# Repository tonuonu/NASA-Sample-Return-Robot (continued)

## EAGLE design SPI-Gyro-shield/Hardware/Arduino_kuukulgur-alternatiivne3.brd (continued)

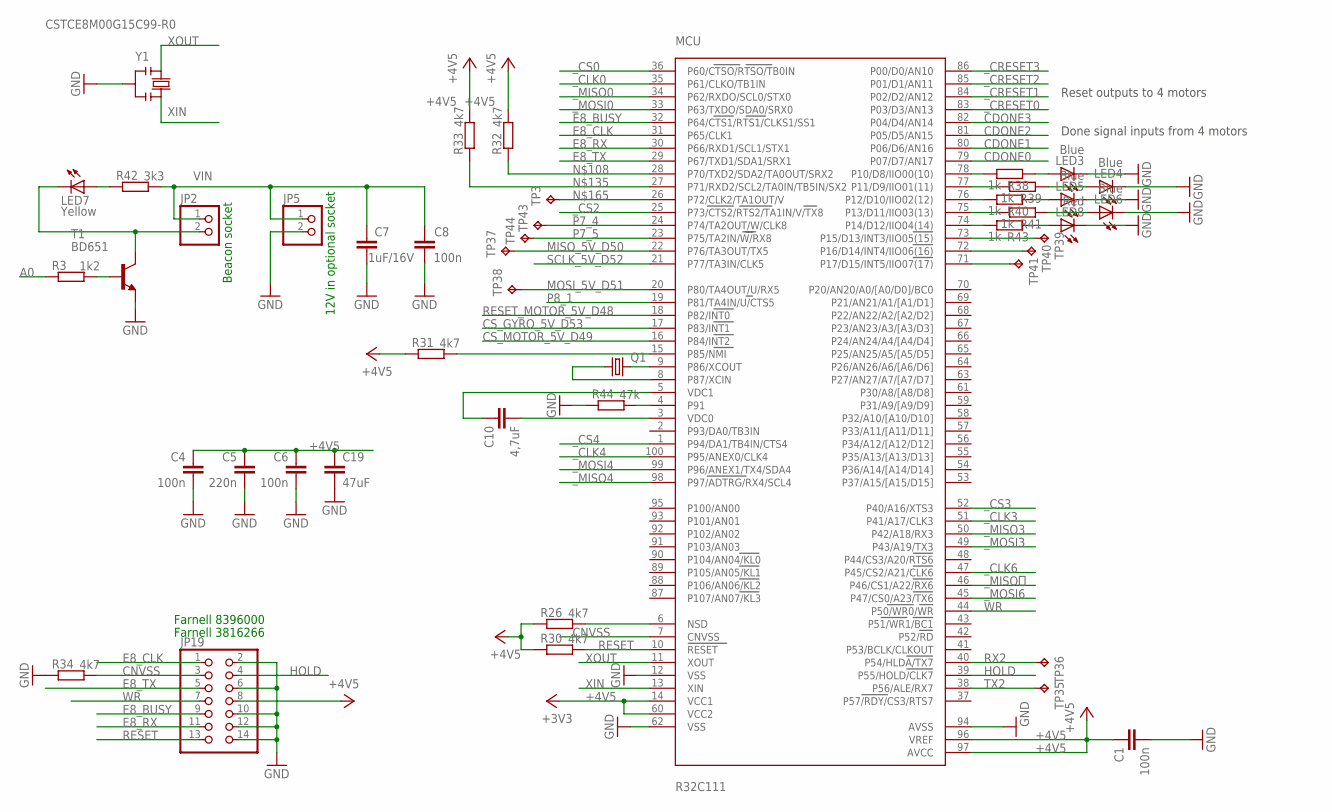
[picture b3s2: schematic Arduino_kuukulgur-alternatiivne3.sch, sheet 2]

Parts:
C1, C4, C6, C8: 100n; C0603-ROUND
C5: 220n; C0603-ROUND
C7: 1uF/16V; C0805
C10: 4,7uF; C0603-ROUND
C19: 47uF; C0805
JP2, JP5: PINHD-1X2; 1X02
JP19: PINHD-2X7; 2X07
LED3, LED4, LED5, LED6: Blue; CHIP-LED0603
LED7: Yellow; CHIP-LED0603
LED8: Red; CHIP-LED0603
MCU: R32C111; 100P6Q-A
Q1: CRYSTALMM20SS; MM20SS
R3: 1k2; R0603-ROUND
R26, R30, R31, R32, R33, R34: 4k7; R0603-ROUND
R38, R39, R40, R41, R43: 1k; R0603-ROUND
R42: 3k3; R0603-ROUND
R44: 47k; R0603-ROUND
T1: BD651; TO220
TP3, TP35, TP36, TP37, TP38, TP39, TP40, TP41, TP43, TP44: TPB1,27; B1,27
Y1: CSTCE8M00G15C99-R0; RESONATOR

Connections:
+4V5: C1.1, C4.1, C5.1, C6.1, C19.1, JP19.8, MCU.14 (VCC1), MCU.60 (VCC2), MCU.96 (VREF), MCU.97 (AVCC), R26.2, R30.2, R31.2, R32.1, R33.1; also elsewhere on the board
A0: R3.2; also elsewhere on the board
CDONE0: MCU.79 (P07/D7/AN17); also elsewhere on the board
CDONE1: MCU.80 (P06/D6/AN16); also elsewhere on the board
CDONE2: MCU.81 (P05/D5/AN15); also elsewhere on the board
CDONE3: MCU.82 (P04/D4/AN14); also elsewhere on the board
CNVSS: JP19.3, MCU.7 (CNVSS), R34.1
CS_GYRO_5V_D53: MCU.17 (P83/INT1); also elsewhere on the board
CS_MOTOR_5V_D49: MCU.16 (P84/INT2); also elsewhere on the board
E8_BUSY: JP19.9, MCU.32 (P64/CTS1/RTS1/CLKS1/SS1); also elsewhere on the board
E8_CLK: JP19.1, MCU.31 (P65/CLK1)
E8_RX: JP19.11, MCU.30 (P66/RXD1/SCL1/STX1); also elsewhere on the board
E8_TX: JP19.5, MCU.29 (P67/TXD1/SDA1/SRX1); also elsewhere on the board
GND: C1.2, C4.2, C5.2, C6.2, C7.2, C8.2, C19.2, JP5.2, JP19.2, JP19.6, JP19.10, JP19.12, JP19.14, LED3.C, LED4.C, LED5.C, LED6.C, LED8.C, MCU.12 (VSS), MCU.62 (VSS), MCU.94 (AVSS), R34.2, R44.2, T1.1 (E), Y1.2; also elsewhere on the board
HOLD: JP19.4, MCU.39 (P55/HOLD/CLK7)
MISO_5V_D50: MCU.22 (P76/TA3OUT/TX5), TP37.TP; also elsewhere on the board
MOSI_5V_D51: MCU.20 (P80/TA4OUT/U/RX5), TP38.TP; also elsewhere on the board
unnamed: C10.1, MCU.5 (VDC1)
unnamed: JP2.2, LED7.C, T1.2 (C)
unnamed: MCU.4 (P91), R44.1
unnamed: C10.2, MCU.3 (VDC0)
unnamed: R3.1, T1.3 (B)
unnamed: MCU.9 (P86/XCOUT), Q1.4 (2)
unnamed: MCU.8 (P87/XCIN), Q1.1
unnamed: MCU.6 (NSD), R26.1
unnamed: MCU.15 (P85/NMI), R31.1
unnamed: LED7.A, R42.2
unnamed: LED3.A, R38.2
unnamed: MCU.28 (P70/TXD2/SDA2/TA0OUT/SRX2), R32.2
unnamed: MCU.27 (P71/RXD2/SCL2/TA0IN/TB5IN/SX2), R33.2
unnamed: LED4.A, R39.2
unnamed: LED5.A, R40.2
unnamed: LED6.A, R41.2
unnamed: MCU.26 (P72/CLK2/TA1OUT/V), TP3.TP
unnamed: LED8.A, R43.2
P1_0: MCU.78 (P10/D8/IIO00(10)), R38.1
P1_1: MCU.77 (P11/D9/IIO01(11)), R39.1
P1_2: MCU.76 (P12/D10/IIO02(12)), R40.1
P1_3: MCU.75 (P13/D11/IIO03(13)), R41.1
P1_4: MCU.74 (P14/D12/IIO04(14)), R43.1
P1_5: MCU.73 (P15/D13/INT3/IIO05(15)), TP39.TP
P1_6: MCU.72 (P16/D14/INT4/IIO06(16)), TP40.TP
P1_7: MCU.71 (P17/D15/INT5/IIO07(17)), TP41.TP
P7_4: MCU.24 (P74/TA2OUT/W/CLK8), TP43.TP
P7_5: MCU.23 (P75/TA2IN/W/RX8), TP44.TP
P8_1: MCU.19 (P81/TA4IN/U/CTS5)
RESET: JP19.13, MCU.10 (RESET), R30.1; also elsewhere on the board
RESET_MOTOR_5V_D48: MCU.18 (P82/INT0); also elsewhere on the board
RX2: MCU.40 (P54/HLDA/TX7), TP36.TP; also elsewhere on the board
SCLK_5V_D52: MCU.21 (P77/TA3IN/CLK5); also elsewhere on the board
TX2: MCU.38 (P56/ALE/RX7), TP35.TP; also elsewhere on the board
VIN: C7.1, C8.1, JP2.1, JP5.1, R42.1; also elsewhere on the board
WR: JP19.7, MCU.44 (P50/WR0/WR)
XIN: MCU.13 (XIN), Y1.3
XOUT: MCU.11 (XOUT), Y1.1
_CLK0: MCU.35 (P61/CLKO/TB1IN); also elsewhere on the board
_CLK3: MCU.51 (P41/A17/CLK3); also elsewhere on the board
_CLK4: MCU.100 (P95/ANEX0/CLK4); also elsewhere on the board
_CLK6: MCU.47 (P45/CS2/A21/CLK6); also elsewhere on the board
_CRESET0: MCU.83 (P03/D3/AN13); also elsewhere on the board
_CRESET1: MCU.84 (P02/D2/AN12); also elsewhere on the board
_CRESET2: MCU.85 (P01/D1/AN11); also elsewhere on the board
_CRESET3: MCU.86 (P00/D0/AN10); also elsewhere on the board
_CS0: MCU.36 (P60/CTSO/RTSO/TB0IN); also elsewhere on the board
_CS2: MCU.25 (P73/CTS2/RTS2/TA1IN/V/TX8); also elsewhere on the board
_CS3: MCU.52 (P40/A16/XTS3); also elsewhere on the board
_CS4: MCU.1 (P94/DA1/TB4IN/CTS4); also elsewhere on the board
_MISO0: MCU.34 (P62/RXDO/SCL0/STX0); also elsewhere on the board
_MISO3: MCU.50 (P42/A18/RX3); also elsewhere on the board
_MISO4: MCU.98 (P97/ADTRG/RX4/SCL4); also elsewhere on the board
_MISO６: MCU.46 (P46/CS1/A22/RX6)
_MOSI0: MCU.33 (P63/TXDO/SDA0/SRX0); also elsewhere on the board
_MOSI3: MCU.49 (P43/A19/TX3); also elsewhere on the board
_MOSI4: MCU.99 (P96/ANEX1/TX4/SDA4); also elsewhere on the board
_MOSI6: MCU.45 (P47/CS0/A23/TX6); also elsewhere on the board

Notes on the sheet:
Farnell 8396000
Farnell 3816266
Beacon socket
12V in optional socket
Reset outputs to 4 motors
Done signal inputs from 4 motors

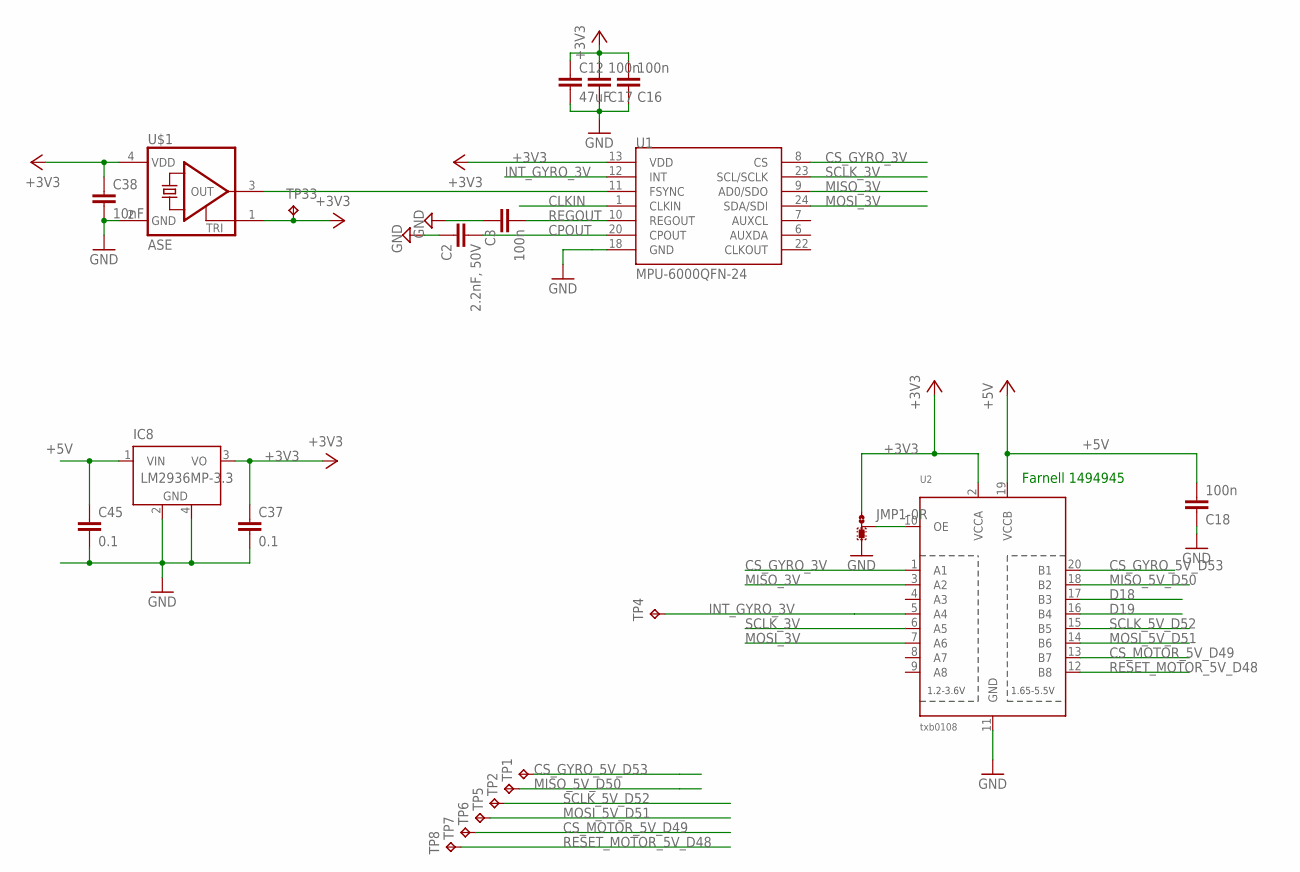
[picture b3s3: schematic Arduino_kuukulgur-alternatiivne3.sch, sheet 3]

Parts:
C2: 2.2nF, 50V; C0603-ROUND
C3, C16, C17, C18: 100n; C0603-ROUND
C12: 47uF; C0805
C37, C45: 0.1; 0603-CAP
C38: 10nF; C0603
IC8: LM2936MP-3.3; SOT223
JMP1: 0R-JUMPB; B0R-JMP
TP1, TP2, TP4, TP5, TP6, TP7, TP8, TP33: TPB1,27; B1,27
U1: MPU-6000QFN-24; QFN-24-TESTING
U2: txb0108; TSSOP20
U$1: ASE

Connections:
+3V3: C12.1, C16.2, C17.2, C37.1, C38.1, IC8.3 (VO), JMP1.1, TP33.TP, U1.13 (VDD), U2.2 (VCCA), U$1.1 (TRI), U$1.4 (VDD); also elsewhere on the board
+5V: C18.2, C45.1, IC8.1 (VIN), U2.19 (VCCB); also elsewhere on the board
CLKIN: U1.1 (CLKIN)
CPOUT: C2.2, U1.20 (CPOUT)
CS_GYRO_3V: U1.8 (CS), U2.1 (A1)
CS_GYRO_5V_D53: TP1.TP, U2.20 (B1); also elsewhere on the board
CS_MOTOR_5V_D49: TP7.TP, U2.13 (B7); also elsewhere on the board
D18: U2.17 (B3); also elsewhere on the board
D19: U2.16 (B4); also elsewhere on the board
GND: C2.1, C3.1, C12.2, C16.1, C17.1, C18.1, C37.2, C38.2, C45.2, IC8.2 (GND), IC8.4 (GND), JMP1.3, U1.18 (GND), U2.11 (GND), U$1.2 (GND); also elsewhere on the board
INT_GYRO_3V: TP4.TP, U1.12 (INT), U2.5 (A4)
MISO_3V: U1.9 (AD0/SDO), U2.3 (A2)
MISO_5V_D50: TP2.TP, U2.18 (B2); also elsewhere on the board
MOSI_3V: U1.24 (SDA/SDI), U2.7 (A6)
MOSI_5V_D51: TP6.TP, U2.14 (B6); also elsewhere on the board
unnamed: JMP1.2, U2.10 (OE)
unnamed: U1.11 (FSYNC), U$1.3 (OUT)
REGOUT: C3.2, U1.10 (REGOUT)
RESET_MOTOR_5V_D48: TP8.TP, U2.12 (B8); also elsewhere on the board
SCLK_3V: U1.23 (SCL/SCLK), U2.6 (A5)
SCLK_5V_D52: TP5.TP, U2.15 (B5); also elsewhere on the board

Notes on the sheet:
Farnell 1494945

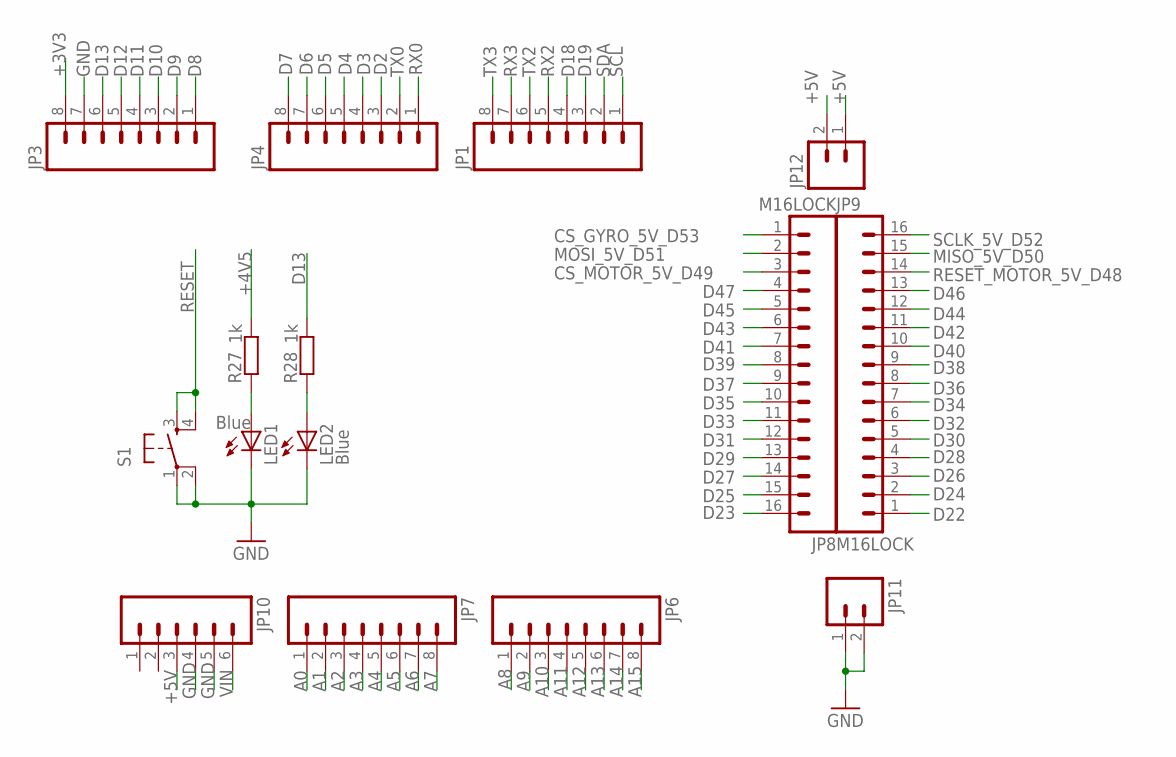
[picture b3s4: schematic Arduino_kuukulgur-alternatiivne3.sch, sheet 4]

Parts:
JP1, JP3, JP4, JP6, JP7: M08LOCK; 1X08_LOCK
JP8, JP9: M16LOCK; 1X16_LOCK
JP10: M06LOCK; 1X06_LOCK
JP11, JP12: M02LOCK; 1X02_LOCK
LED1, LED2: Blue; CHIP-LED0603
R27, R28: 1k; R0603-ROUND
S1: TAC_SWITCHPTH; TACTILE-PTH

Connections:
+3V3: JP3.8; also elsewhere on the board
+4V5: R27.1; also elsewhere on the board
+5V: JP10.3, JP12.1, JP12.2; also elsewhere on the board
A0: JP7.1; also elsewhere on the board
A1: JP7.2
A2: JP7.3; also elsewhere on the board
A3: JP7.4; also elsewhere on the board
A4: JP7.5; also elsewhere on the board
A5: JP7.6; also elsewhere on the board
A6: JP7.7; also elsewhere on the board
A7: JP7.8; also elsewhere on the board
A8: JP6.1
A9: JP6.2
A10: JP6.3
A11: JP6.4
A12: JP6.5
A13: JP6.6
A14: JP6.7
A15: JP6.8
CS_GYRO_5V_D53: JP8.1; also elsewhere on the board
CS_MOTOR_5V_D49: JP8.3; also elsewhere on the board
D2: JP4.3; also elsewhere on the board
D3: JP4.4; also elsewhere on the board
D4: JP4.5; also elsewhere on the board
D5: JP4.6; also elsewhere on the board
D6: JP4.7; also elsewhere on the board
D7: JP4.8; also elsewhere on the board
D8: JP3.1; also elsewhere on the board
D9: JP3.2; also elsewhere on the board
D10: JP3.3; also elsewhere on the board
D11: JP3.4; also elsewhere on the board
D12: JP3.5; also elsewhere on the board
D13: JP3.6, R28.1
D18: JP1.4; also elsewhere on the board
D19: JP1.3; also elsewhere on the board
D22: JP9.1
D23: JP8.16
D24: JP9.2
D25: JP8.15
D26: JP9.3
D27: JP8.14
D28: JP9.4
D29: JP8.13
D30: JP9.5
D31: JP8.12
D32: JP9.6
D33: JP8.11
D34: JP9.7
D35: JP8.10
D36: JP9.8
D37: JP8.9
D38: JP9.9
D39: JP8.8
D40: JP9.10
D41: JP8.7
D42: JP9.11
D43: JP8.6; also elsewhere on the board
D44: JP9.12; also elsewhere on the board
D45: JP8.5; also elsewhere on the board
D46: JP9.13; also elsewhere on the board
D47: JP8.4; also elsewhere on the board
GND: JP3.7, JP10.4, JP10.5, JP11.1, JP11.2, LED1.C, LED2.C, S1.1, S1.2; also elsewhere on the board
MISO_5V_D50: JP9.15; also elsewhere on the board
MOSI_5V_D51: JP8.2; also elsewhere on the board
unnamed: LED1.A, R27.2
unnamed: LED2.A, R28.2
RESET: S1.3, S1.4; also elsewhere on the board
RESET_MOTOR_5V_D48: JP9.14; also elsewhere on the board
RX0: JP4.1
RX2: JP1.5; also elsewhere on the board
RX3: JP1.7
SCL: JP1.1
SCLK_5V_D52: JP9.16; also elsewhere on the board
SDA: JP1.2
TX0: JP4.2
TX2: JP1.6; also elsewhere on the board
TX3: JP1.8
VIN: JP10.6; also elsewhere on the board

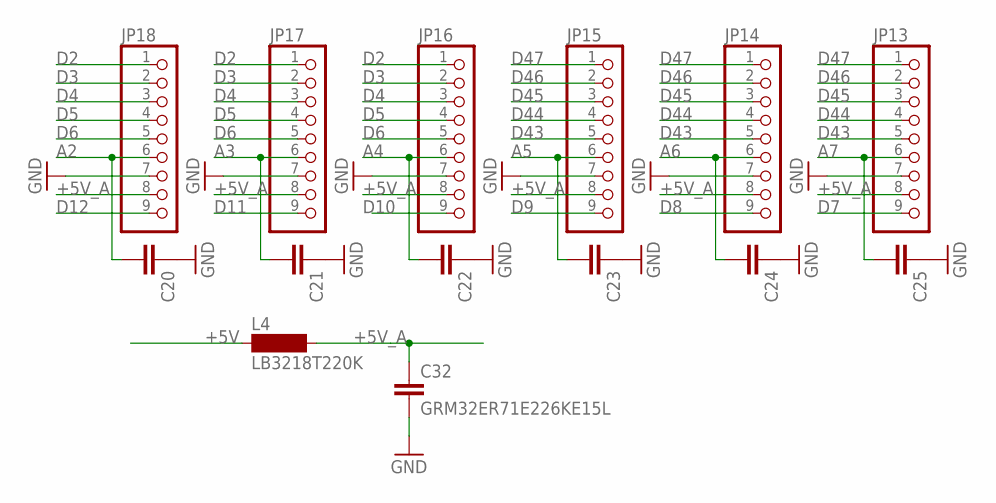
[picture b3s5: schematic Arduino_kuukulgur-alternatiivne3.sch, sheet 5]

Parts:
C20, C21, C22, C23, C24, C25: C-EUC0603; C0603
C32: GRM32ER71E226KE15L; C1210
JP13, JP14, JP15, JP16, JP17, JP18: PINHD-1X9; 1X09
L4: LB3218T220K; SM-1206

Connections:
+5V: L4.1; also elsewhere on the board
+5V_A: C32.1, JP13.8, JP14.8, JP15.8, JP16.8, JP17.8, JP18.8, L4.2
A2: C20.2, JP18.6; also elsewhere on the board
A3: C21.2, JP17.6; also elsewhere on the board
A4: C22.2, JP16.6; also elsewhere on the board
A5: C23.2, JP15.6; also elsewhere on the board
A6: C24.2, JP14.6; also elsewhere on the board
A7: C25.2, JP13.6; also elsewhere on the board
D2: JP16.1, JP17.1, JP18.1; also elsewhere on the board
D3: JP16.2, JP17.2, JP18.2; also elsewhere on the board
D4: JP16.3, JP17.3, JP18.3; also elsewhere on the board
D5: JP16.4, JP17.4, JP18.4; also elsewhere on the board
D6: JP16.5, JP17.5, JP18.5; also elsewhere on the board
D7: JP13.9; also elsewhere on the board
D8: JP14.9; also elsewhere on the board
D9: JP15.9; also elsewhere on the board
D10: JP16.9; also elsewhere on the board
D11: JP17.9; also elsewhere on the board
D12: JP18.9; also elsewhere on the board
D43: JP13.5, JP14.5, JP15.5; also elsewhere on the board
D44: JP13.4, JP14.4, JP15.4; also elsewhere on the board
D45: JP13.3, JP14.3, JP15.3; also elsewhere on the board
D46: JP13.2, JP14.2, JP15.2; also elsewhere on the board
D47: JP13.1, JP14.1, JP15.1; also elsewhere on the board
GND: C20.1, C21.1, C22.1, C23.1, C24.1, C25.1, C32.2, JP13.7, JP14.7, JP15.7, JP16.7, JP17.7, JP18.7; also elsewhere on the board

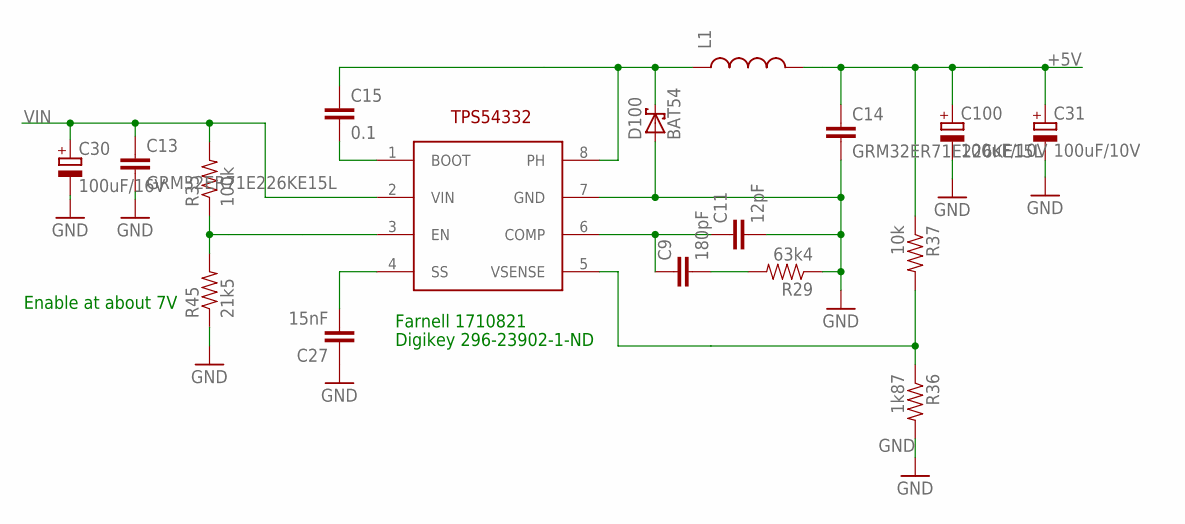
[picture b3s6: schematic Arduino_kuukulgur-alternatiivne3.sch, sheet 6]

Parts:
C9: 180pF; 0603-CAP
C11: 12pF; 0603-CAP
C13, C14: GRM32ER71E226KE15L; C1210
C15: 0.1; 0603-CAP
C27: 15nF; 0603-CAP
C30: 100uF/16V; C/6032-28R
C31, C100: 100uF/10V; C/6032-28R
D100: BAT54; SOT23
L1: INDUCTORSRU1038; SRU1038
R29: 63k4; 0603-RES
R35: 100k; 0603-RES
R36: 1k87; 0603-RES
R37: 10k; 0603-RES
R45: 21k5; 0603-RES
U$3: TPS54332; SO8

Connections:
+5V: C14.1, C31.+, C100.+, L1.2, R37.1; also elsewhere on the board
ENABLE_PANDA: R35.1, R45.2, U$3.3 (EN)
GND: C11.2, C13.2, C14.2, C27.1, C30.-, C31.-, C100.-, D100.1 (A), R29.1, R36.2, R45.1, U$3.7 (GND); also elsewhere on the board
unnamed: C27.2, U$3.4 (SS)
unnamed: C9.1, C11.1, U$3.6 (COMP)
unnamed: C9.2, R29.2
unnamed: C15.2, U$3.1 (BOOT)
unnamed: R36.1, R37.2, U$3.5 (VSENSE)
unnamed: C15.1, D100.3 (C), L1.1, U$3.8 (PH)
VIN: C13.1, C30.+, R35.2, U$3.2 (VIN); also elsewhere on the board

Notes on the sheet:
Farnell 1710821
Digikey 296-23902-1-ND
Enable at about 7V

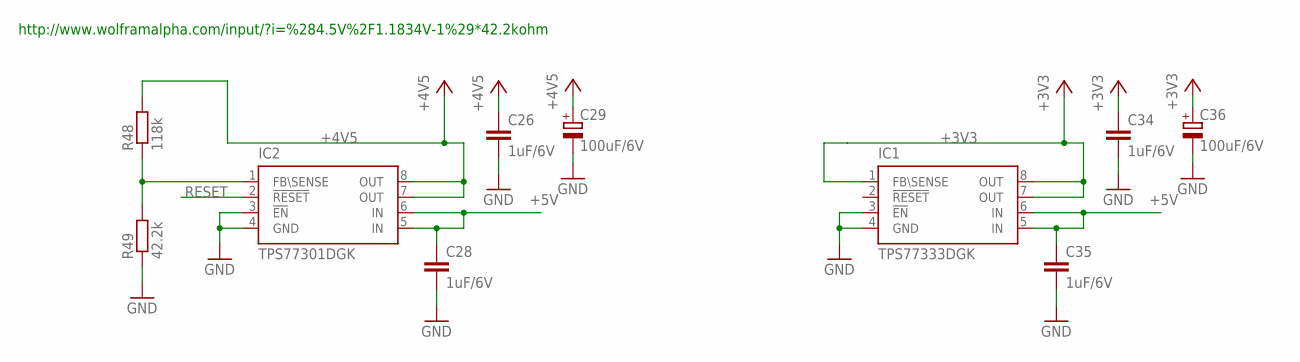
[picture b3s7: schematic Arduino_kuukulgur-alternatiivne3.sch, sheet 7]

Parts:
C26, C28, C34, C35: 1uF/6V; C0603
C29, C36: 100uF/6V; C/6032-28R
IC1: TPS77333DGK; MSOP8
IC2: TPS77301DGK; MSOP8
R48: 118k; R0603
R49: 42.2k; R0603

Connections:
+3V3: C34.1, C36.+, IC1.1 (FB\SENSE), IC1.7 (OUT), IC1.8 (OUT); also elsewhere on the board
+4V5: C26.1, C29.+, IC2.7 (OUT), IC2.8 (OUT), R48.2; also elsewhere on the board
+5V: C28.1, C35.1, IC1.5 (IN), IC1.6 (IN), IC2.5 (IN), IC2.6 (IN); also elsewhere on the board
GND: C26.2, C28.2, C29.-, C34.2, C35.2, C36.-, IC1.3 (!EN), IC1.4 (GND), IC2.3 (!EN), IC2.4 (GND), R49.1; also elsewhere on the board
unnamed: IC2.1 (FB\SENSE), R48.1, R49.2
RESET: IC2.2 (!RESET); also elsewhere on the board

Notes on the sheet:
http://www.wolframalpha.com/input/?i=%284.5V%2F1.1834V-1%29*42.2kohm

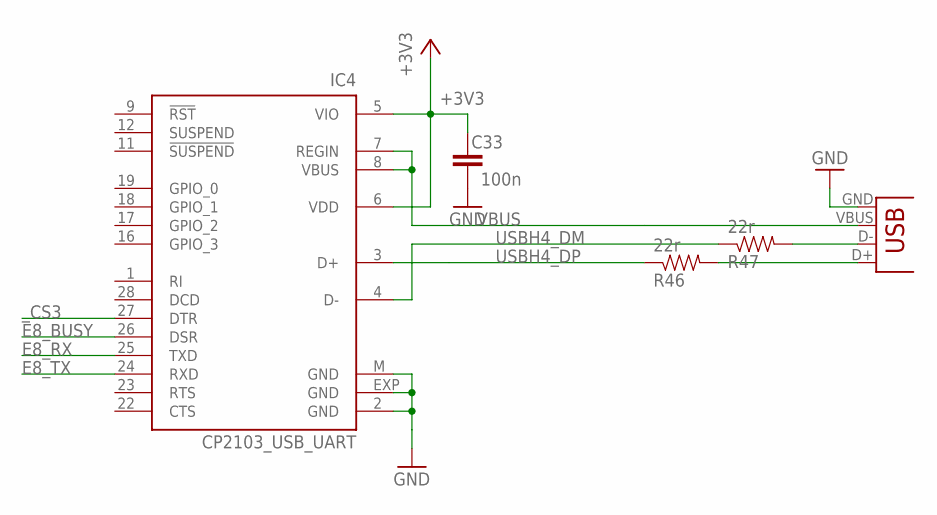
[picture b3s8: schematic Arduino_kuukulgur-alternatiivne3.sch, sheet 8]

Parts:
C33: 100n; C0603-ROUND
IC4: CP2103_USB_UART; MLP28
R46, R47: 22r; 0805
X2: USBSMD; USB-MINIB

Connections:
+3V3: C33.1, IC4.5 (VIO), IC4.6 (VDD); also elsewhere on the board
D+: R46.2, X2.D+
D-: R47.2, X2.D-
E8_BUSY: IC4.26 (DSR); also elsewhere on the board
E8_RX: IC4.25 (TXD); also elsewhere on the board
E8_TX: IC4.24 (RXD); also elsewhere on the board
GND: C33.2, IC4.2 (GND), IC4.EXP (GND), IC4.M (GND), X2.GND; also elsewhere on the board
USBH4_DM: IC4.4 (D-), R47.1
USBH4_DP: IC4.3 (D+), R46.1
VBUS: IC4.7 (REGIN), IC4.8 (VBUS), X2.VBUS
_CS3: IC4.27 (DTR); also elsewhere on the board

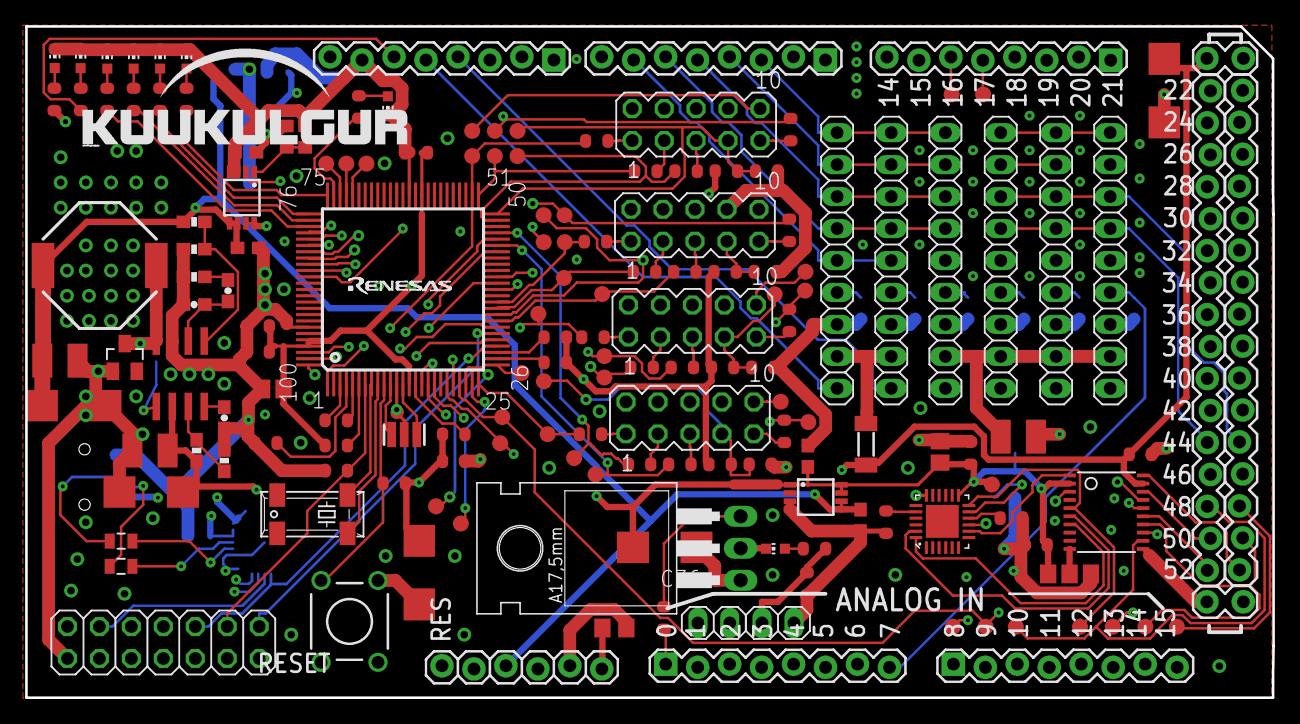
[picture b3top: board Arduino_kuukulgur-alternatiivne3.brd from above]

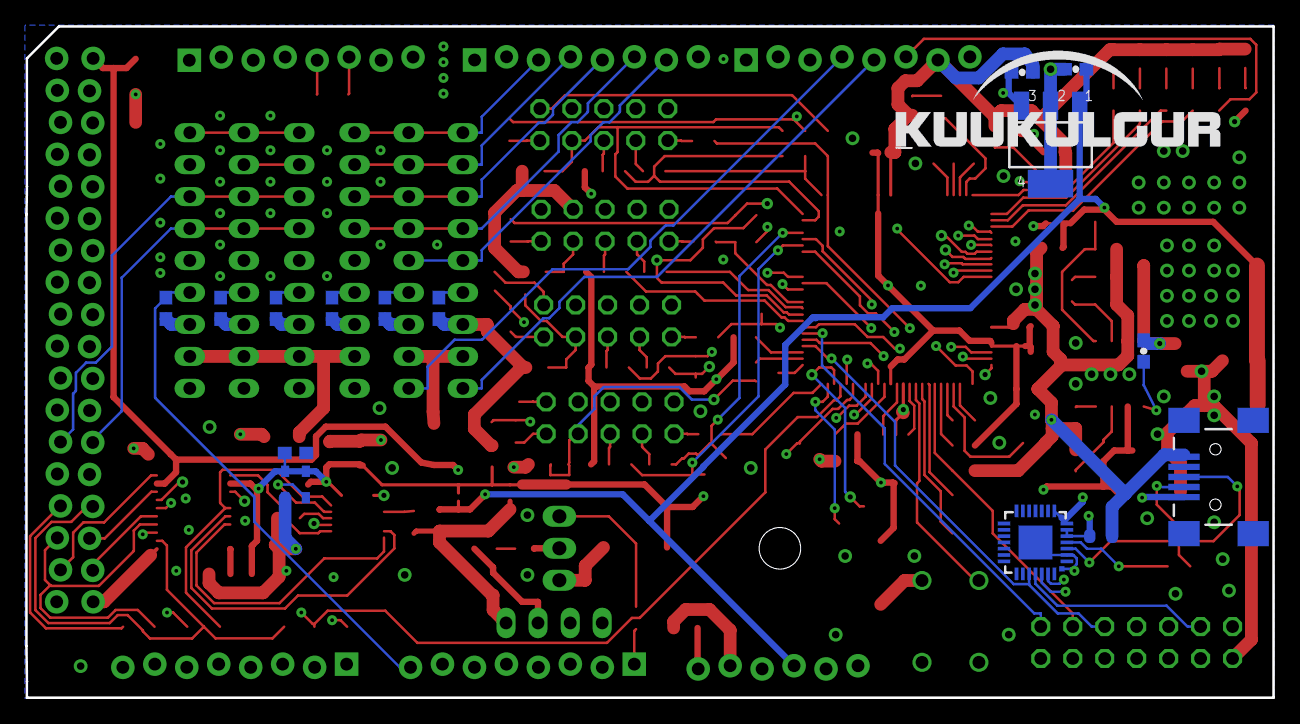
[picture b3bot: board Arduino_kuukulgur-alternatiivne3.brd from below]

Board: 4 copper layers, 99.1 x 53.3 mm, 180 parts (15 on the bottom side), 142 nets.

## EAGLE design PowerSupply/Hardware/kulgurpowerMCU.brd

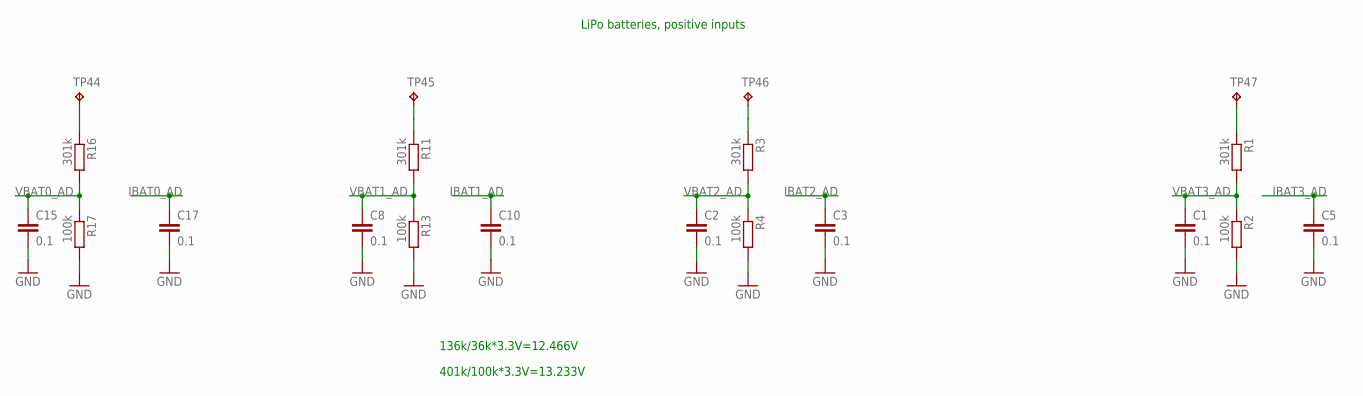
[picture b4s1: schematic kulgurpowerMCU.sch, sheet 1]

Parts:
C1, C2, C3, C5, C8, C10, C15, C17: 0.1; C0603
R1, R3, R11, R16: 301k; R0603
R2, R4, R13, R17: 100k; R0603
TP44, TP45, TP46, TP47: TPB1,27; B1,27

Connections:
GND: C1.2, C2.2, C3.2, C5.2, C8.2, C10.2, C15.2, C17.2, R2.2, R4.2, R13.2, R17.2; also elsewhere on the board
IBAT0_AD: C17.1; also elsewhere on the board
IBAT1_AD: C10.1; also elsewhere on the board
IBAT2_AD: C3.1; also elsewhere on the board
IBAT3_AD: C5.1; also elsewhere on the board
unnamed: R3.1, TP46.TP
unnamed: R11.1, TP45.TP
unnamed: R16.1, TP44.TP
unnamed: R1.1, TP47.TP
VBAT0_AD: C15.1, R16.2, R17.1; also elsewhere on the board
VBAT1_AD: C8.1, R11.2, R13.1; also elsewhere on the board
VBAT2_AD: C2.1, R3.2, R4.1; also elsewhere on the board
VBAT3_AD: C1.1, R1.2, R2.1; also elsewhere on the board

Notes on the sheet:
LiPo batteries, positive inputs
136k/36k*3.3V=12.466V
401k/100k*3.3V=13.233V

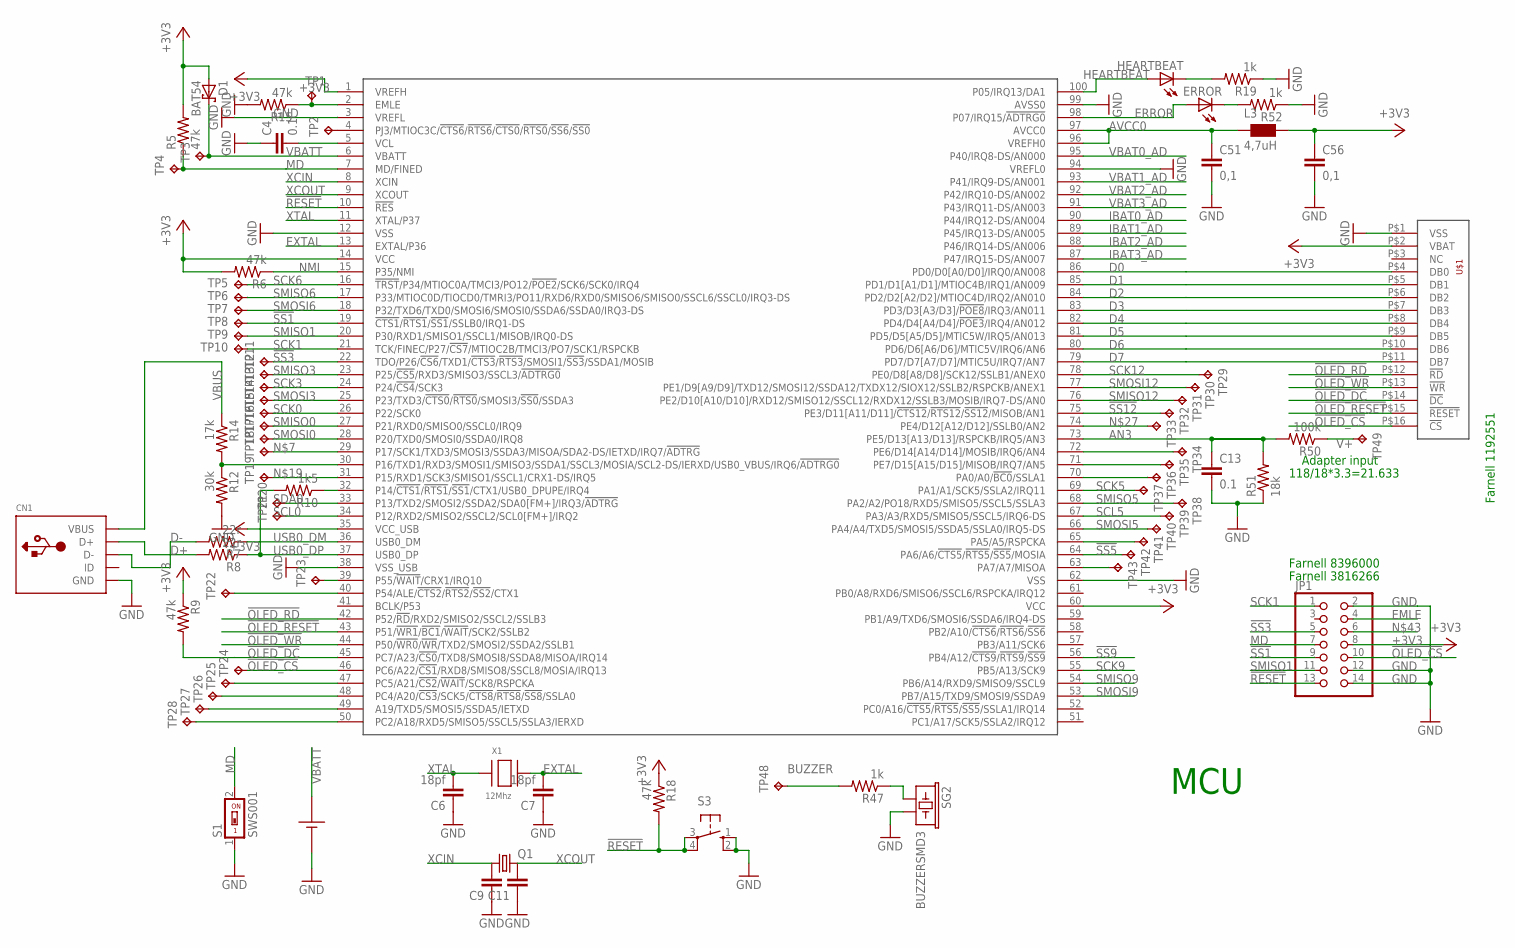
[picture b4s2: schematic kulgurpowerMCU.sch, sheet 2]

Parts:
C4, C13: 0.1; 0603-CAP
C6, C7: 18pf; 0603-CAP
C9, C11: CAP0603-CAP; 0603-CAP
C51, C56: 0,1; 0603-CAP
CN1: USBMINIB; USB-MINIB
D1: BAT54; SOT23
ERROR: LED0603; LED-0603
HEARTBEAT: LED0603; LED-0603
JP1: PINHD-2X7; 2X07
L3: 4,7uH; WE-KI_0805_B
Q1: CRYSTALMM20SS; MM20SS
R5, R6, R9, R15, R18: 47k; 0603-RES
R7, R8: 22r; 0603-RES
R10: 1k5; 0603-RES
R12: 30k; 0603-RES
R14: 17k; 0603-RES
R19, R47, R52: 1k; 0603-RES
R50: 100k; 0603-RES
R51: 18k; 0603-RES
S1: SWS001; SMS-001
S3: 10-XX; B3F-10XX
SG2: BUZZERSMD3; BUZZER-CMT1102
TP1, TP2, TP3, TP4: TPB2,54; B2,54
TP5, TP6, TP7, TP8, TP9, TP10, TP11, TP12, TP13, TP14, TP15, TP16, TP17, TP18, TP19, TP20, TP21, TP22, TP23, TP24, TP25, TP26, TP27, TP28, TP29, TP30, TP31, TP32, TP33, TP34, TP35, TP36, TP37, TP38, TP39, TP40, TP41, TP42, TP43, TP48, TP49: TPB1,27; B1,27
U$1: ER-OLEDM032-1
U$2: EDLRD224V3R6C
U$14: R5F5630ADDFP; LTQFP100
X1: 12Mhz; NX5032

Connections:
!OLED_CS: JP1.10, TP24.TP, U$1.P$16 (!CS), U$14.46 (PC6/A22/!CS1!/RXD8/SMISO8/SSCL8/MOSIA/I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)
!OLED_DC: R9.2, U$1.P$14 (!DC), U$14.45 (PC7/A23/!CS0!/TXD8/SMOSI8/SSDA8/MISOA/I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)
!OLED_RD: U$1.P$12 (!RD), U$14.42 (P52/!RD!/RXD2/SMISO2/SSCL2/SSLB3)
!OLED_RESET: U$1.P$15 (!RESET), U$14.43 (P51/!WR1!/!BC1!/!WAIT!/SCK2/SSLB2)
!OLED_WR: U$1.P$13 (!WR), U$14.44 (P50/!WR0!/!WR!/TXD2/SMOSI2/SSDA2/SSLB1)
!RESET: JP1.13, R18.2, S3.3, S3.4 (P1), U$14.10 (!RES!); also elsewhere on the board
!SS1: JP1.9, TP8.TP, U$14.19 (!CTS1!/!RTS1!/!SS1!/SSLB0/IRQ1-DS)
!SS3: JP1.5, TP11.TP, U$14.22 (TDO/P26/!CS6!/TXD1/!CTS3!/!RTS3!/SMOSI1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)
!SS5: TP42.TP, U$14.64 (PA6/A6/!CTS5!/!RTS5!/!SS5!/MOSIA)
!SS9: U$14.56 (PB4/A12/!CTS9!/!RTS9!/!SS9!)
!SS12: TP32.TP, U$14.75 (PE3/D11[A11/D11]/!CTS12!/!RTS12!/!SS12!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)
+3V3: C56.1, D1.1 (A), JP1.8, L3.1 (2), R5.2, R6.2, R9.1, R18.1, U$1.P$2 (VBAT), U$14.1 (VREFH), U$14.14 (VCC), U$14.35 (VCC_USB), U$14.60 (VCC); also elsewhere on the board
AN3: C13.1, R50.2, R51.2, U$14.73 (PE5/D13[A13/D13]/RSPCKB/IRQ5/AN3)
AVCC0: C51.1, L3.2 (1), U$14.96 (VREFH0), U$14.97 (AVCC0)
BUZZER: R47.2, TP48.TP
D0: U$1.P$4 (DB0), U$14.86 (PD0/D0[A0/D0]/IRQ0/AN008)
D1: U$1.P$5 (DB1), U$14.85 (PD1/D1[A1/D1]/MTIOC4B/IRQ1/AN009)
D2: U$1.P$6 (DB2), U$14.84 (PD2/D2[A2/D2]/MTIOC4D/IRQ2/AN010)
D3: U$1.P$7 (DB3), U$14.83 (PD3/D3[A3/D3]/!POE8!/IRQ3/AN011)
D4: U$1.P$8 (DB4), U$14.82 (PD4/D4[A4/D4]/!POE3!/IRQ4/AN012)
D5: U$1.P$9 (DB5), U$14.81 (PD5/D5[A5/D5]/MTIC5W/IRQ5/AN013)
D6: U$1.P$10 (DB6), U$14.80 (PD6/D6[A6/D6]/MTIC5V/IRQ6/AN6)
D7: U$1.P$11 (DB7), U$14.79 (PD7/D7[A7/D7]/MTIC5U/IRQ7/AN7)
D+: CN1.D+, R8.2
D-: CN1.D-, R7.2
EMLE: JP1.4, R15.1, TP1.TP, U$14.2 (EMLE)
EN_PANDA: R47.1, SG2.1
ERROR: ERROR.A, U$14.98 (P07/IRQ15/!ADTRG0)
EXTAL: C7.2, U$14.13 (EXTAL/P36), X1.P$2
GND: C4.1, C6.1, C7.1, C9.1, C11.1, C13.2, C51.2, C56.2, CN1.GND, JP1.2, JP1.12, JP1.14, R12.2, R15.2, R19.1, R51.1, R52.1, S1.1, S3.1 (S), S3.2 (S1), SG2.2, U$1.P$1 (VSS), U$2.N, U$14.3 (VREFL), U$14.12 (VSS), U$14.38 (VSS_USB), U$14.62 (VSS), U$14.94 (VREFL0), U$14.99 (AVSS0); also elsewhere on the board
HEARTBEAT: HEARTBEAT.A, U$14.100 (P05/IRQ13/DA1)
IBAT0_AD: U$14.90 (P44/IRQ12-DS/AN004); also elsewhere on the board
IBAT1_AD: U$14.89 (P45/IRQ13-DS/AN005); also elsewhere on the board
IBAT2_AD: U$14.88 (P46/IRQ14-DS/AN006); also elsewhere on the board
IBAT3_AD: U$14.87 (P47/IRQ15-DS/AN007); also elsewhere on the board
MD: JP1.7, R5.1, S1.2, TP4.TP, U$14.7 (MD/FINED)
unnamed: R10.1, U$14.32 (P14/!CTS1!/!RTS1!/!SS1!/CTX1/USB0_DPUPE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)
unnamed: R12.1, R14.2, U$14.30 (P16/TXD1/RXD3/SMOSI1/SMISO3/SSDA1/SSCL3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)
unnamed: C4.2, U$14.5 (VCL)
unnamed: TP18.TP, U$14.29 (P17/SCK1/TXD3/SMOSI3/SSDA3/MISOA/SDA2-D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)
unnamed: TP25.TP, U$14.47 (PC5/A21/!CS2!/!WAIT!/SCK8/RSPCKA)
unnamed: TP26.TP, U$14.48 (PC4/A20/!CS3!/SCK5/!CTS8!/!RTS8!/!SS8!/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)
unnamed: TP27.TP, U$14.49 (A19/TXD5/SMOSI5/SSDA5/IETXD)
unnamed: HEARTBEAT.C, R19.2
unnamed: TP28.TP, U$14.50 (PC2/A18/RXD5/SMISO5/SSCL5/SSLA3/IERXD)
unnamed: TP19.TP, U$14.31 (P15/RXD1/SCK3/SMISO1/SSCL1/CRX1-DS/IRQ5)
unnamed: TP2.TP, U$14.4 (PJ3/MTIOC3C/!CTS6!/!RTS6!/!CTS0!/!RTS0!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)
unnamed: TP22.TP, U$14.40 (P54/ALE/!CTS2!/!RTS2!/!SS2!/CTX1)
unnamed: TP33.TP, U$14.74 (PE4/D12[A12/D12]/SSLB0/AN2)
unnamed: TP23.TP, U$14.39 (P55/!WAIT!/CRX1/IRQ10)
unnamed: ERROR.C, R52.2
unnamed: TP34.TP, U$14.72 (PE6/D14[A14/D14]/MOSIB/IRQ6/AN4)
unnamed: TP35.TP, U$14.71 (PE7/D15[A15/D15]/MISOB/IRQ7/AN5)
unnamed: TP36.TP, U$14.70 (PA0/A0/!BC0!/SSLA1)
unnamed: TP41.TP, U$14.65 (PA5/A5/RSPCKA)
unnamed: TP43.TP, U$14.63 (PA7/A7/MISOA)
NMI: R6.1, U$14.15 (P35/NMI)
SCK0: TP15.TP, U$14.26 (P22/SCK0)
SCK1: JP1.1, TP10.TP, U$14.21 (TCK/FINEC/P27/!CS7!/MTIOC2B/TMCI3/PO7/S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)
SCK3: TP13.TP, U$14.24 (P24/!CS4!/SCK3)
SCK5: TP37.TP, U$14.69 (PA1/A1/SCK5/SSLA2/IRQ11)
SCK6: TP5.TP, U$14.16 (!TRST!/P34/MTIOC0A/TMCI3/PO12/!POE2!/SC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)
SCK9: U$14.55 (PB5/A13/SCK9)
SCK12: TP29.TP, U$14.78 (PE0/D8[A8/D8]/SCK12/SSLB1/ANEX0)
SCL0: TP21.TP, U$14.34 (P12/RXD2/SMISO2/SSCL2/SCL0[FM+]/IRQ2)
SCL5: TP39.TP, U$14.67 (PA3/A3/RXD5/SMISO5/SSCL5/IRQ6-DS)
SDA0: TP20.TP, U$14.33 (P13/TXD2/SMOSI2/SSDA2/SDA0[FM+]/IRQ3/!A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)
SMISO0: TP16.TP, U$14.27 (P21/RXD0/SMISO0/SSCL0/IRQ9)
SMISO1: JP1.11, TP9.TP, U$14.20 (P30/RXD1/SMISO1/SSCL1/MISOB/IRQ0-DS)
SMISO3: TP12.TP, U$14.23 (P25/!CS5!/RXD3/SMISO3/SSCL3/!ADTRG0!)
SMISO5: TP38.TP, U$14.68 (PA2/A2/PO18/RXD5/SMISO5/SSCL5/SSLA3)
SMISO6: TP6.TP, U$14.17 (P33/MTIOC0D/TIOCD0/TMRI3/PO11/RXD6/RXD0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)
SMISO9: U$14.54 (PB6/A14/RXD9/SMISO9/SSCL9)
SMISO12: TP31.TP, U$14.76 (PE2/D10[A10/D10]/RXD12/SMISO12/SSCL12/R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)
SMOSI0: TP17.TP, U$14.28 (P20/TXD0/SMOSI0/SSDA0/IRQ8)
SMOSI3: TP14.TP, U$14.25 (P23/TXD3/!CTS0!/!RTS0!/SMOSI3/!SS0!/SSD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)
SMOSI5: TP40.TP, U$14.66 (PA4/A4/TXD5/SMOSI5/SSDA5/SSLA0/IRQ5-DS)
SMOSI6: TP7.TP, U$14.18 (P32/TXD6/TXD0/SMOSI6/SMOSI0/SSDA6/SSDA0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)
SMOSI9: U$14.53 (PB7/A15/TXD9/SMOSI9/SSDA9)
SMOSI12: TP30.TP, U$14.77 (PE1/D9[A9/D9]/TXD12/SMOSI12/SSDA12/TXDX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)
USB0_DM: R7.1, U$14.36 (USB0_DM)
USB0_DP: R8.1, R10.2, U$14.37 (USB0_DP)
V+: R50.1, TP49.TP
VBAT0_AD: U$14.95 (P40/IRQ8-DS/AN000); also elsewhere on the board
VBAT1_AD: U$14.93 (P41/IRQ9-DS/AN001); also elsewhere on the board
VBAT2_AD: U$14.92 (P42/IRQ10-DS/AN002); also elsewhere on the board
VBAT3_AD: U$14.91 (P43/IRQ11-DS/AN003); also elsewhere on the board
VBATT: D1.3 (C), TP3.TP, U$2.P, U$14.6 (VBATT)
VBUS: CN1.VBUS, R14.1; also elsewhere on the board
XCIN: C9.2, Q1.1, U$14.8 (XCIN)
XCOUT: C11.2, Q1.4 (2), U$14.9 (XCOUT)
XTAL: C6.2, U$14.11 (XTAL/P37), X1.P$1

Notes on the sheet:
MCU
Farnell 1192551
Farnell 8396000
Farnell 3816266
Adapter input
118/18*3.3=21.633

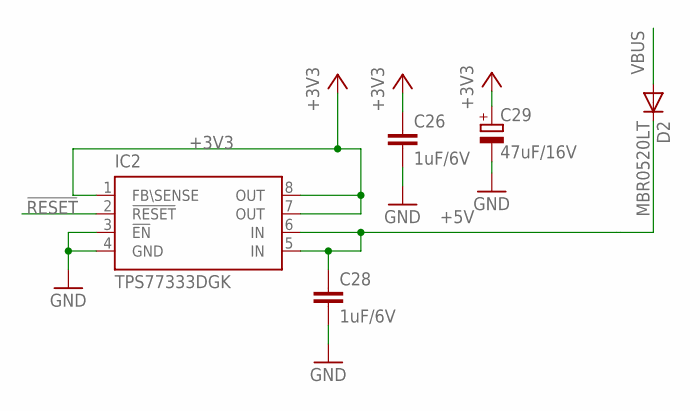
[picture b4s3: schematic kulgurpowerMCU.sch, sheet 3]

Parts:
C26, C28: 1uF/6V; C0603
C29: 47uF/16V; C/6032-28R
D2: MBR0520LT; SOD123
IC2: TPS77333DGK; MSOP8

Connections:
!RESET: IC2.2 (!RESET); also elsewhere on the board
+3V3: C26.1, C29.+, IC2.1 (FB\SENSE), IC2.7 (OUT), IC2.8 (OUT); also elsewhere on the board
+5V: C28.1, D2.C, IC2.5 (IN), IC2.6 (IN)
GND: C26.2, C28.2, C29.-, IC2.3 (!EN), IC2.4 (GND); also elsewhere on the board
VBUS: D2.A; also elsewhere on the board

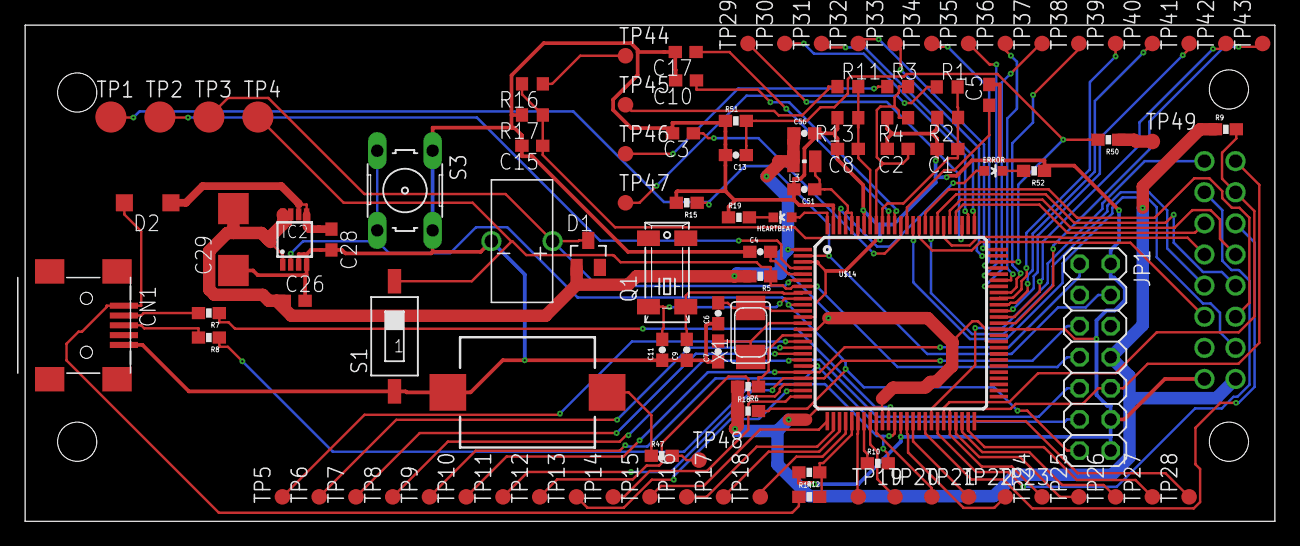
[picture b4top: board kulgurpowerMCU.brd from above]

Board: 2 copper layers, 102.0 x 40.5 mm, 107 parts (0 on the bottom side), 93 nets.
